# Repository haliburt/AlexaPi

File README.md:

# AlexaPi
The software connects the ESP8266 to both WiFi and the MQTT server (hosted by homeassistant). The hardware is used to create wireless smart switches for a home automation project.

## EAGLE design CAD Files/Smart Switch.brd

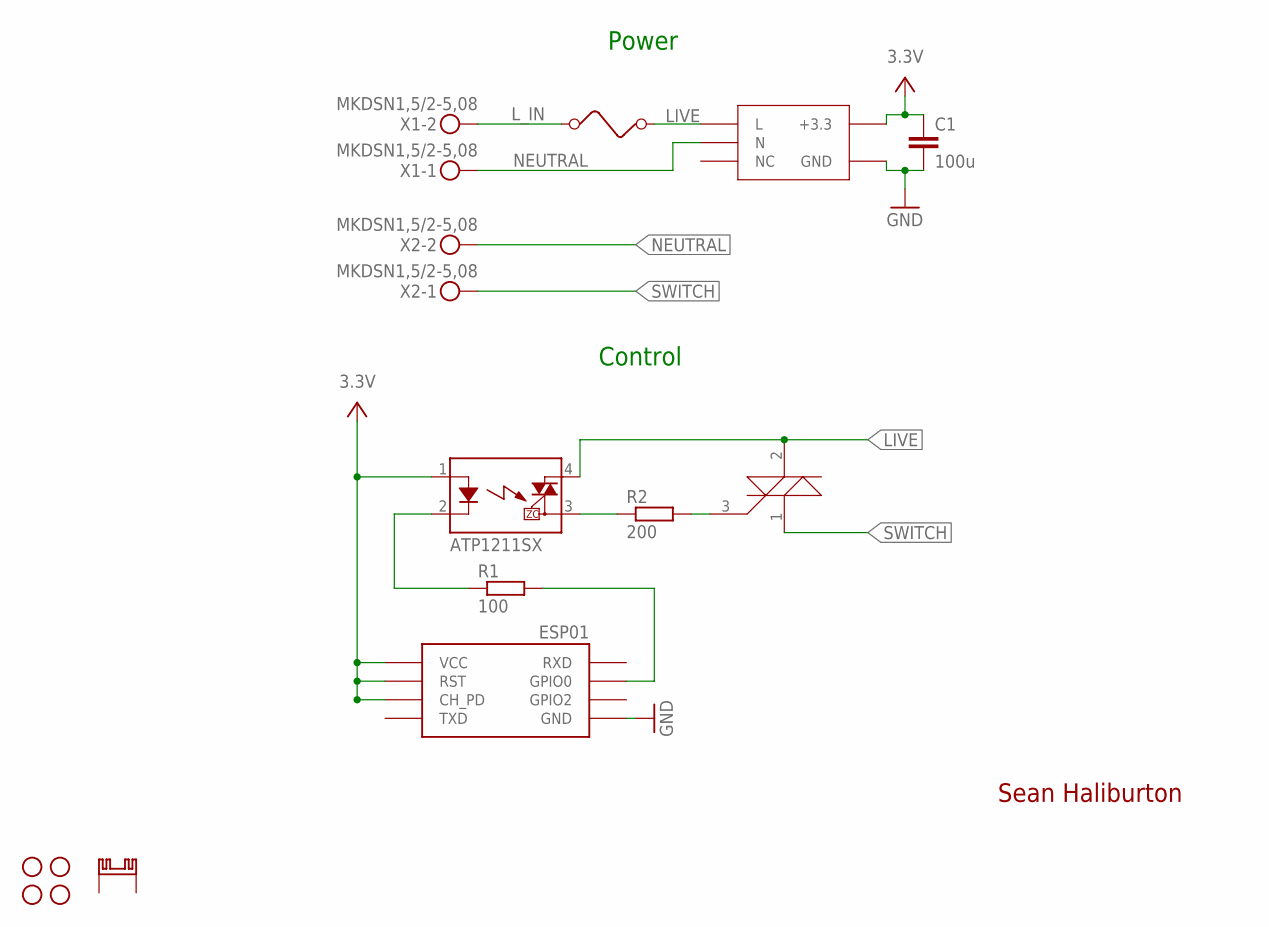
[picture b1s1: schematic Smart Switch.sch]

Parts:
C1: 100u; C0805
H1, H2, H3, H4: STAND-OFF
K1: ATP1211SX; SOP04
R1: 100; R0805
R2: 200; R0805
U$1: ESP01
U$2: RAC04-GB
U$3: BTA16; TO220V
U$4: FUSE
U$5: RA-T2X-38E; SK129
X1, X2: MKDSN1,5/2-5,08

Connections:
GND: C1.2, U$1.GND, U$2.GND
GPIO0: R1.2, U$1.GPIO0
LIVE: K1.4 (DS1), U$2.L, U$3.2 (A2), U$4.P$2 (2)
L_IN: U$4.P$1 (1), X1.2
unnamed: K1.2 (K), R1.1
unnamed: K1.3 (DS2), R2.1
unnamed: R2.2, U$3.3 (G)
NEUTRAL: U$2.N, X1.1, X2.2
SWITCH: U$3.1 (A1), X2.1
VCC: C1.1, K1.1 (A), U$1.CH_PD, U$1.RST, U$1.VCC, U$2.3.3 (+3.3)

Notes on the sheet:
Sean Haliburton
Power
Control

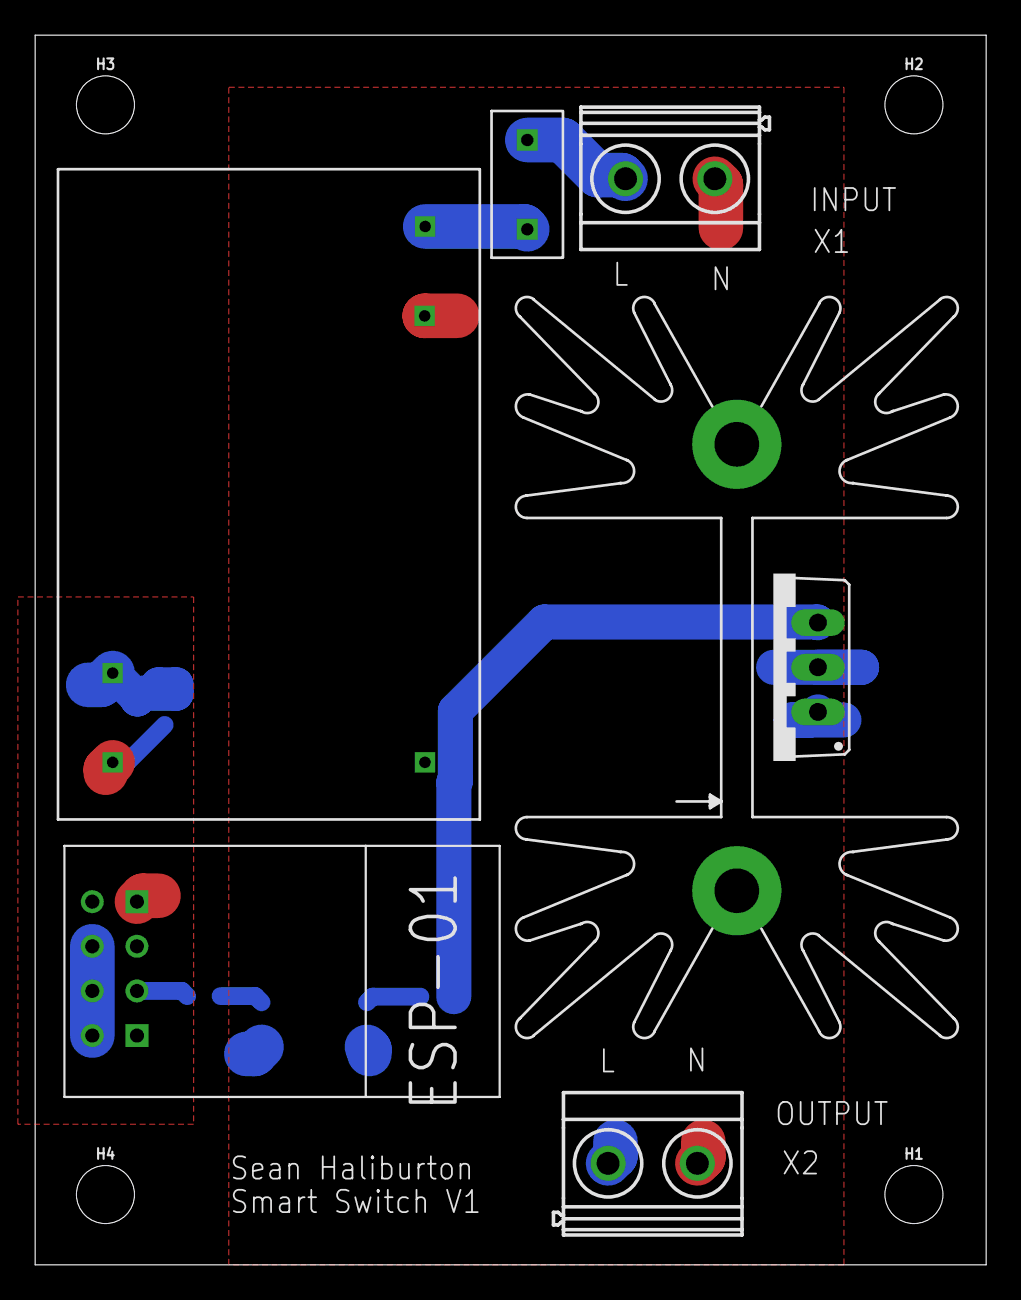
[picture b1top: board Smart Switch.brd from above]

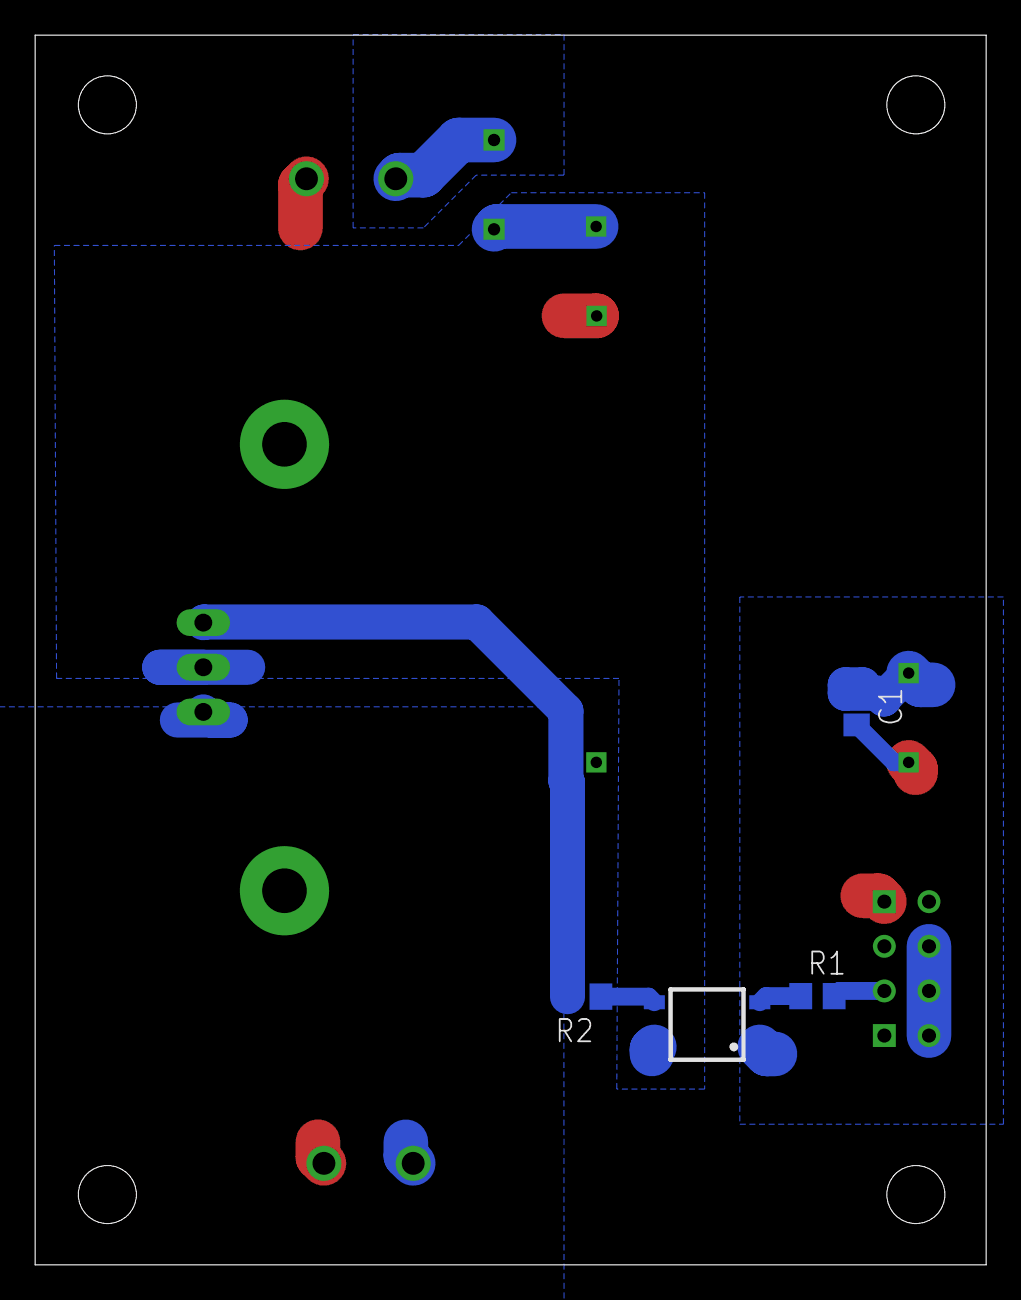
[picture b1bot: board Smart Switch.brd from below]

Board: 2 copper layers, 54.1 x 70.0 mm, 15 parts (4 on the bottom side), 10 nets.

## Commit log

2017-09-14 First version of smart switch control
2017-09-14 Initial hardware design for smart switches
2017-09-14 Added first version of the schematic
2017-09-14 Added pdf of schematic
2017-09-18 Added final schematic and board layout
2017-09-18 Added pdf of designs
2017-10-10 Transformerless AC-DC converter
    - Added the spice simulation. Real design needs a fuse on the live line and an X Rated capacitor; I will need to research if it is possible to drop that much voltage across one of these capacitors. M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
    *Will look into adding a series capacitor to the neutral side, as well as a filter for possible high frequency voltage spikes on the main lines.
    **Circuit is no longer galvanically isolated from mains power and is more dangerous. Do not work on the circuit when it is live. As a result this will be the last thing I implement
2017-10-11 Changed most of the design
    Replaced relay with triac and opto isolator
    Replaced transformer with alternative AC-DC converter
2017-11-06 Revision was sent for manufacturing

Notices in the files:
parts and their libraries:
SparkFun-Hardware: Licensing: Creative Commons ShareAlike 4.0 International - https://creativecommons.org/licenses/by-sa/4.0
